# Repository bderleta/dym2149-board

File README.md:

# dym2149-board
Dual YM2149 synth board design using retro technology (THT elements, DIP packages)

An application of ATMega32 8-bit MCU in PDIP package capable of driving two of YM2149 PSG chips. [Reference firmware](https://github.com/bderleta/dym2149-firmware-ph) is just passing packets to selected PSG, but possibilities are very wide.

# Revision 2 changes

-  `U595_SRCLR` and `U595_RCLK` are swapped, to put `RCLK` to pin `OC0`, allowing to strobe `RCLK` pin from Timer0 compare output. This way the onboard shift register can be driven fully asynchronously, as `SRCLK` and `SER` are driven by SPI peripheral. Attention must be paid when SRAM/flash is used in the application.
- `YM1_BC1` and `YM1_SEL` are swapped, to put `YM1_SEL` to pin `OC1B`, allowing to switch `YM1_SEL` pin from Timer1 compare output. `YM2_SEL` is already on `OC1A` in all revisions. As `SEL` pin divides internal PSG clock by 2, in theory it should also divide an output frequency by 2, leading to sound an octave lower than before, although it has to be tested if any interesting effects can be obtained this way.
- Placement of I2C and UART ports has been slightly changed.

# Features

- ATMega32 MCU in PDIP package, clocked with external 16MHz crystal oscillator
- 10 pin ISP (KANDA) and JTAG ports 
- Two sockets for YM2149 PSG chips, independent control lines, shared data/address line
- DIP8 socket for SPI flash/RAM
- 595 shift register with 8 pin output header, controlled via SPI, for debugging/driving peripherals
- Headers for both I/O ports of each PSG
- 32768 Hz secondary oscillator for CPU Timer2
- Requires DIP8/DIP14 CXO for clocking YM chips
- Revision 1a/2 design features separate [mixer board](https://github.com/bderleta/dym2149-oric-mixer) to enable developing various output stages (different chip/channel assignments, active opamp stage, etc)

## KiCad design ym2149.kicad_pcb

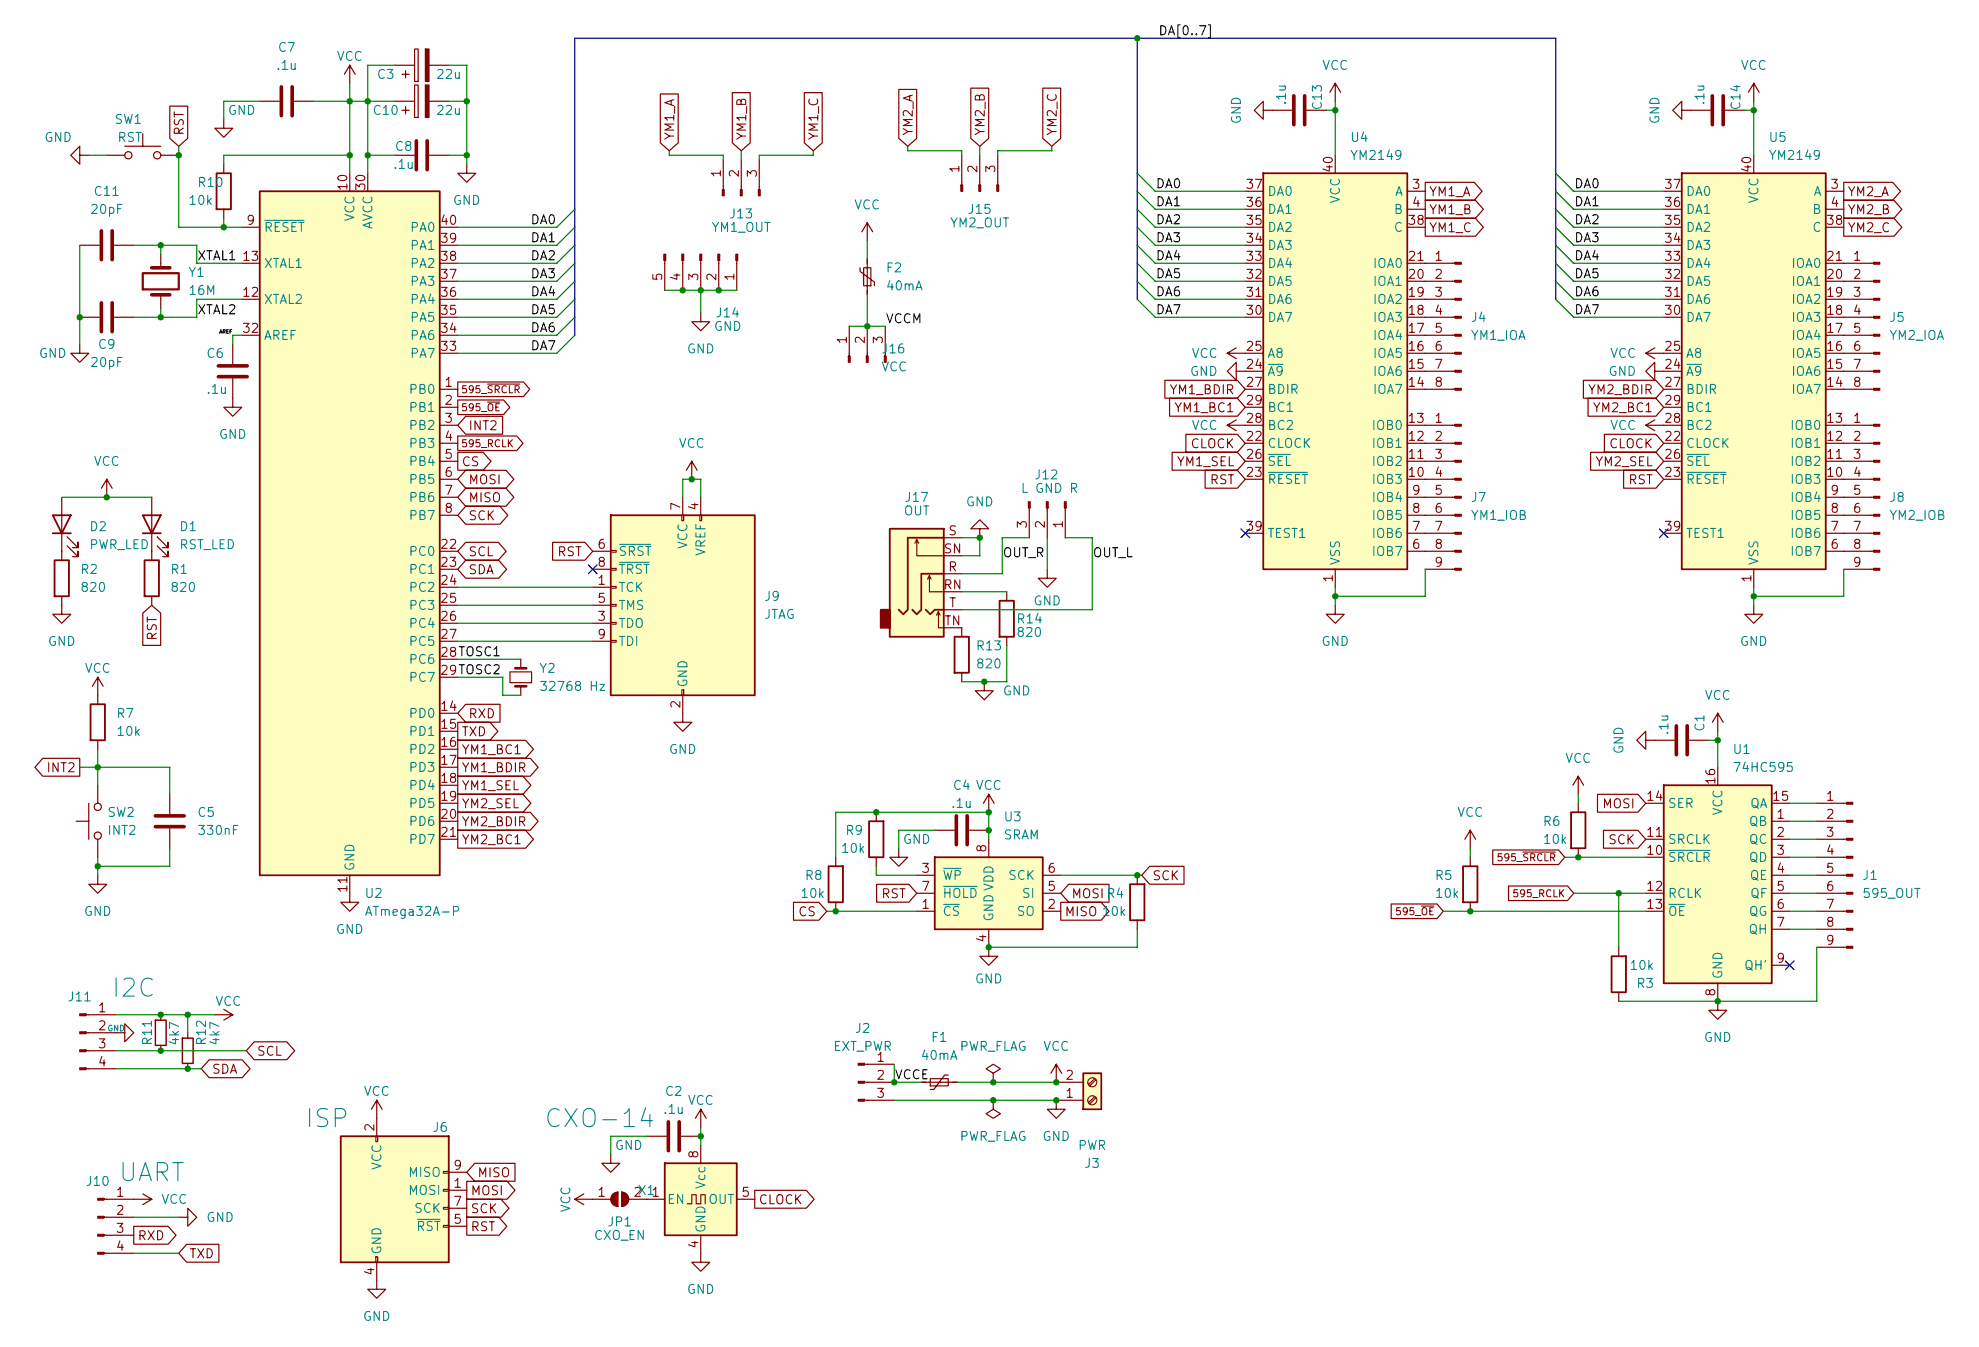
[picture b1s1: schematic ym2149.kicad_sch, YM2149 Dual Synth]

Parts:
C1, C2, C4, C6, C7, C8, C13, C14: .1u; C_Disc_D5.0mm_W2.5mm_P5.00mm
C3, C10: 22u; CP_Radial_D7.5mm_P2.50mm
C5: 330nF; C_Disc_D3.8mm_W2.6mm_P2.50mm
C9, C11: 20pF; C_Disc_D4.3mm_W1.9mm_P5.00mm
D1: RST_LED; LED_D3.0mm
D2: PWR_LED; LED_D3.0mm
F1, F2: 40mA; Fuse_BelFuse_0ZRE0005FF_L8.3mm_W3.8mm
J1: 595_OUT; PinHeader_1x09_P2.54mm_Vertical
J2: EXT_PWR; PinHeader_1x03_P2.54mm_Vertical
J3: PWR; TerminalBlock_Phoenix_PT-1,5-2-5.0-H_1x02_P5.00mm_Horizontal
J4: YM1_IOA; PinHeader_1x08_P2.54mm_Vertical
J5: YM2_IOA; PinHeader_1x08_P2.54mm_Vertical
J6: ISP; IDC-Header_2x05_P2.54mm_Vertical
J7: YM1_IOB; PinHeader_1x09_P2.54mm_Vertical
J8: YM2_IOB; PinHeader_1x09_P2.54mm_Vertical
J9: JTAG; IDC-Header_2x05_P2.54mm_Vertical
J10: UART; PinHeader_1x04_P2.54mm_Vertical
J11: I2C; PinHeader_1x04_P2.54mm_Vertical
J12: L GND R; PinHeader_1x03_P2.54mm_Vertical
J13: YM1_OUT; PinHeader_1x03_P2.54mm_Vertical
J14: GND; PinHeader_1x05_P2.54mm_Vertical
J15: YM2_OUT; PinHeader_1x03_P2.54mm_Vertical
J16: VCC; PinHeader_1x03_P2.54mm_Vertical
J17: OUT; Jack_6.35mm_Neutrik_NMJ6HFD2-AU_Horizontal
JP1: CXO_EN; SolderJumper-2_P1.3mm_Open_RoundedPad1.0x1.5mm
R1, R2, R13, R14: 820; R_Axial_DIN0207_L6.3mm_D2.5mm_P10.16mm_Horizontal
R3, R4, R5, R6, R7, R8, R9, R10: 10k; R_Axial_DIN0204_L3.6mm_D1.6mm_P5.08mm_Horizontal
R11, R12: 4k7; R_Axial_DIN0204_L3.6mm_D1.6mm_P5.08mm_Horizontal
SW1: RST; SW_PUSH_6mm
SW2: INT2; SW_PUSH_6mm
U1: 74HC595; DIP-16_W7.62mm_Socket
U2: ATmega32A-P; DIP-40_W15.24mm_Socket
U3: SRAM; DIP-8_W7.62mm_Socket
U4, U5: YM2149; DIP-40_W15.24mm_Socket
X1: CXO-14; CXO-14-8
Y1: 16M; Crystal_HC49-4H_Vertical
Y2: 32768 Hz; Crystal_AT310_D3.0mm_L10.0mm_Vertical

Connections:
595_RCLK: R3.2, U1.12 (RCLK), U2.4 (PB3)
595_~OE: R5.2, U1.13 (~OE), U2.2 (PB1)
595_~SRCLR: R6.2, U1.10 (~SRCLR), U2.1 (PB0)
/AREF: C6.2, U2.32 (AREF)
/DA0: U2.40 (PA0), U4.37 (DA0), U5.37 (DA0)
/DA1: U2.39 (PA1), U4.36 (DA1), U5.36 (DA1)
/DA2: U2.38 (PA2), U4.35 (DA2), U5.35 (DA2)
/DA3: U2.37 (PA3), U4.34 (DA3), U5.34 (DA3)
/DA4: U2.36 (PA4), U4.33 (DA4), U5.33 (DA4)
/DA5: U2.35 (PA5), U4.32 (DA5), U5.32 (DA5)
/DA6: U2.34 (PA6), U4.31 (DA6), U5.31 (DA6)
/DA7: U2.33 (PA7), U4.30 (DA7), U5.30 (DA7)
/OUT_L: J12.1, J17.T
/OUT_R: J12.3, J17.R
/TOSC1: U2.28 (PC6), Y2.2
/TOSC2: U2.29 (PC7), Y2.1
/VCCE: F1.1, J2.1, J2.2
/VCCM: F2.1, J16.1, J16.2, J16.3
/XTAL1: C11.2, U2.13 (XTAL1), Y1.2
/XTAL2: C9.2, U2.12 (XTAL2), Y1.1
CLOCK: U4.22 (CLOCK), U5.22 (CLOCK), X1.5 (OUT)
CS: R8.1, U2.5 (PB4), U3.1 (~CS)
GND: C1.1, C2.2, C3.2, C4.2, C5.2, C6.1, C7.2, C8.2, C9.1, C10.2, C11.1, C13.1, C14.1, J1.9, J2.3, J3.1, J6.4 (GND), J6.6 (GND), J6.8 (GND), J6.10 (GND), J7.9, J8.9, J9.2 (GND), J9.10 (GND), J10.2, J11.2, J12.2, J14.1, J14.2, J14.3, J14.4, J14.5, J17.S, J17.SN, R2.2, R3.1, R4.1, R13.2, R14.2, SW1.1, SW2.1, U1.8 (GND), U2.11 (GND), U2.31 (GND), U3.4 (GND), U4.1 (VSS), U4.24 (~A9), U5.1 (VSS), U5.24 (~A9), X1.4 (GND); also elsewhere on the board
INT2: C5.1, R7.2, SW2.2, U2.3 (PB2)
MISO: J6.9 (MISO), U2.7 (PB6), U3.2 (SO)
MOSI: J6.1 (MOSI), U1.14 (SER), U2.6 (PB5), U3.5 (SI)
unnamed: D1.1 (K), R1.1
unnamed: D2.1 (K), R2.1
unnamed: J1.1, U1.15 (QA)
unnamed: J1.2, U1.1 (QB)
unnamed: J1.3, U1.2 (QC)
unnamed: J1.4, U1.3 (QD)
unnamed: J1.5, U1.4 (QE)
unnamed: J1.6, U1.5 (QF)
unnamed: J1.7, U1.6 (QG)
unnamed: J1.8, U1.7 (QH)
unnamed: J4.1, U4.21 (IOA0)
unnamed: J4.2, U4.20 (IOA1)
unnamed: J4.3, U4.19 (IOA2)
unnamed: J4.4, U4.18 (IOA3)
unnamed: J4.5, U4.17 (IOA4)
unnamed: J4.6, U4.16 (IOA5)
unnamed: J4.7, U4.15 (IOA6)
unnamed: J4.8, U4.14 (IOA7)
unnamed: J5.1, U5.21 (IOA0)
unnamed: J5.2, U5.20 (IOA1)
unnamed: J5.3, U5.19 (IOA2)
unnamed: J5.4, U5.18 (IOA3)
unnamed: J5.5, U5.17 (IOA4)
unnamed: J5.6, U5.16 (IOA5)
unnamed: J5.7, U5.15 (IOA6)
unnamed: J5.8, U5.14 (IOA7)
unnamed: J7.1, U4.13 (IOB0)
unnamed: J7.2, U4.12 (IOB1)
unnamed: J7.3, U4.11 (IOB2)
unnamed: J7.4, U4.10 (IOB3)
unnamed: J7.5, U4.9 (IOB4)
unnamed: J7.6, U4.8 (IOB5)
unnamed: J7.7, U4.7 (IOB6)
unnamed: J7.8, U4.6 (IOB7)
unnamed: J8.1, U5.13 (IOB0)
unnamed: J8.2, U5.12 (IOB1)
unnamed: J8.3, U5.11 (IOB2)
unnamed: J8.4, U5.10 (IOB3)
unnamed: J8.5, U5.9 (IOB4)
unnamed: J8.6, U5.8 (IOB5)
unnamed: J8.7, U5.7 (IOB6)
unnamed: J8.8, U5.6 (IOB7)
unnamed: J9.1 (TCK), U2.24 (PC2)
unnamed: J9.3 (TDO), U2.26 (PC4)
unnamed: J9.5 (TMS), U2.25 (PC3)
unnamed: J9.9 (TDI), U2.27 (PC5)
unnamed: J17.RN, R14.1
unnamed: J17.TN, R13.1
unnamed: JP1.2 (B), X1.1 (EN)
unnamed: R9.1, U3.3 (~WP)
RST: J6.5 (~RST), J9.6 (~SRST), R1.2, R10.2, SW1.2, U2.9 (~RESET), U3.7 (~HOLD), U4.23 (~RESET), U5.23 (~RESET)
RXD: J10.3, U2.14 (PD0)
SCK: J6.7 (SCK), R4.2, U1.11 (SRCLK), U2.8 (PB7), U3.6 (SCK)
SCL: J11.3, R11.2, U2.22 (PC0)
SDA: J11.4, R12.2, U2.23 (PC1)
TXD: J10.4, U2.15 (PD1)
VCC: C1.2, C2.1, C3.1, C4.1, C7.1, C8.1, C10.1, C13.2, C14.2, D1.2 (A), D2.2 (A), F1.2, F2.2, J3.2, J6.2 (VCC), J9.4 (VREF), J9.7 (VCC), J10.1, J11.1, JP1.1 (A), R5.1, R6.1, R7.1, R8.2, R9.2, R10.1, R11.1, R12.1, U1.16 (VCC), U2.10 (VCC), U2.30 (AVCC), U3.8 (VDD), U4.25 (A8), U4.28 (BC2), U4.40 (VCC), U5.25 (A8), U5.28 (BC2), U5.40 (VCC), X1.8 (Vcc)
YM1_A: J13.1, U4.3 (A)
YM1_B: J13.2, U4.4 (B)
YM1_BC1: U2.16 (PD2), U4.29 (BC1)
YM1_BDIR: U2.17 (PD3), U4.27 (BDIR)
YM1_C: J13.3, U4.38 (C)
YM1_SEL: U2.18 (PD4), U4.26 (~SEL)
YM2_A: J15.1, U5.3 (A)
YM2_B: J15.2, U5.4 (B)
YM2_BC1: U2.21 (PD7), U5.29 (BC1)
YM2_BDIR: U2.20 (PD6), U5.27 (BDIR)
YM2_C: J15.3, U5.38 (C)
YM2_SEL: U2.19 (PD5), U5.26 (~SEL)

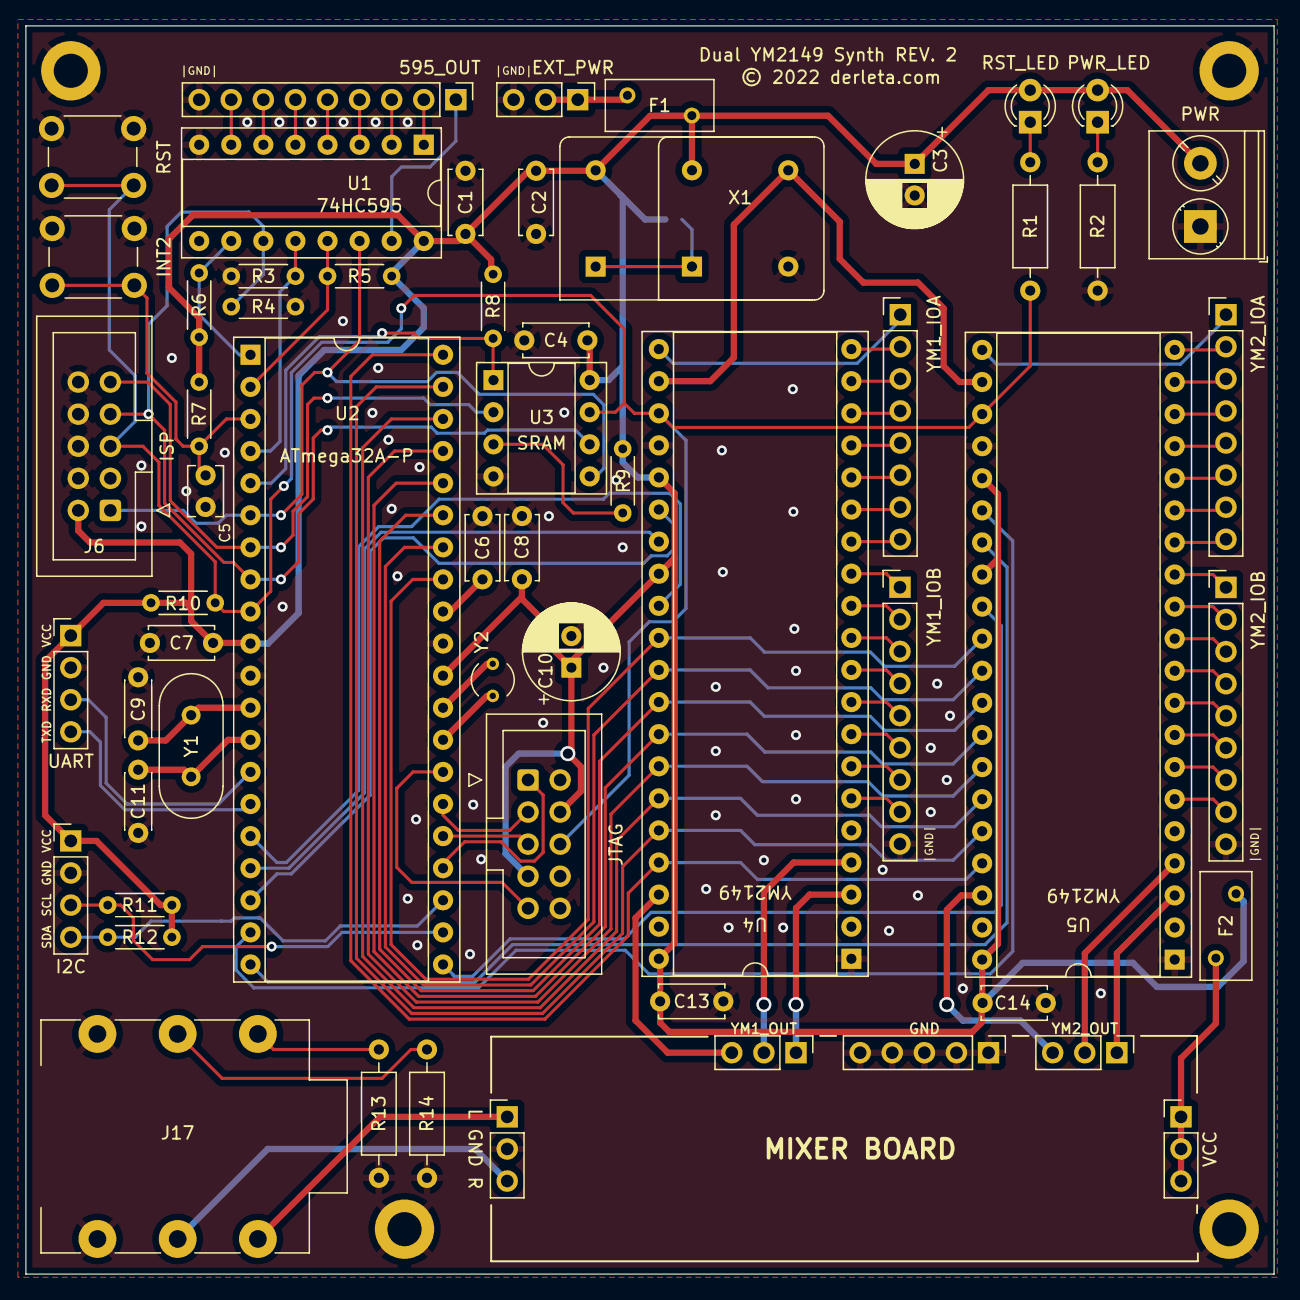
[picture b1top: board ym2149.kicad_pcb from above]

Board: 2 copper layers, 98.8 x 98.8 mm, 63 parts (1 on the bottom side), 95 nets.

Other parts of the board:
MH1, MH2, MH3, MH4: MountingHole_2.7mm_M2.5_DIN965_Pad

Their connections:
GND: MH1.1, MH2.1, MH3.1, MH4.1; also elsewhere on the board

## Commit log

2023-01-01 Revision 1a

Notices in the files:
ym2149.kicad_pcb:
© 2022 derleta.com
